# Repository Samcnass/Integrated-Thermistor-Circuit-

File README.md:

# Integrated Thermistor Circuit-
Class/Personal project for an analog integrated thermistor circuit that measures temperature using a simple comparison system with visual feedback using LEDs and console output. 

## Project Overview 

The circuit continuously reads:
- A desired temperature, set using a 10kΩ dial potentiometer
- The room's (or object if attached) temperature with a 10kΩ thermistor (Calibrated using thermometer data)

The system compares the two temperatures and will light up:
- Red LED: if it is too hot
- Blue LED: if it is too cold
- Green LED: if it is just right (within range set in code)

This project is great because it blends analog components, component calibration, and simple boolean logic using an Arduino. It is also easily expandable to other projects. 

A full schematic, PCB design, and Arduino IDE code are available via included folders. 

## Components required for project

| Component                      | Quantity |
|-------------------------------|----------|
| Arduino Uno or Nano           | 1        |
| 10kΩ Analog Thermistor        | 1        |
| 10kΩ Dial Potentiometer       | 1        |
| 10kΩ Resistor                 | 1        |
| 330Ω Resistors                | 3        |
| LEDs (Red, Green, Blue)       | 3        |
| Breadboard + Jumper Wires     | as needed |

## Circuit Description 

- The thermistor forms a voltage divider with a 10kΩ resistor, which is then connected to an analog pin to read temperature
- A dial potentiometer is used to set a desired temperature range from the user 
- The Arduino will compare the thermistor and potentiometer readings and will light up an LED to indicate:
  - **Too cold**: Thermistor reading below lower threshold
  - **Too hot**: Thermistor reading above upper threshold
  - **Just right**: Reading within user-defined range

## Circuit Schematic 

full schematic available in /schematic/ folder. 
This can be opened in KiCAD for viewing.
You can also view the schematic pdf in said folder for easy viewing.
The schematic was done outside of class and was part of a personal project. 

## PCB
Full PCB file is available in /PCB/ folder. 
This can be opened in KiCAD for viewing.
You can also view the PCB png for easy viewing.
The PCB was designed as part of a personal project.

## Arduino IDE Code 

Arduino code to read and compare values is found in the /Code/ folder.
The code includes:
- variable to set desired range (ex: range=3, temperature range is plus or minus 3 away from desired temperature)
- Analog to voltage conversion function for easy reading
- LED boolean logic
- Analog inputs from thermistor and potentiometer
- Calibrated thermistor function to convert voltage to temperature (change depending on thermistor)
- Console output depending on temperature comparison

## Calibration 
The thermistor was calibrated using temperature data from a thermometer.  
There is a Microsoft Excel file located in the /Documents/ folder as well as a png of the calibration plot. 
You may change your thermistor calibration as you see fit

---

## Images
An image of the real-world circuit is in the /Images/ folder. The image is of an Arduino Uno but can be changed with an Arduino Nano if needed. 

## How to use 
1. Wire the circuit according to the schematic
2. Change desired temperature range within code 
3. Upload the code to your board
4. Turn the dial to set your desired temperature 
5. Observe LEDs and Arduino console for live output

## Future Improvements
- Add OLED display for real-time temperature readout instead of using console
- Implement circuit onto a complete PCB board and implement in thermodynamics experiements
  
## License
This project is open-source under the LICENSE

-- 

## Other project uses
I have used this circuit to measure the temperature of a refrigerator to study its heating/cooling processes as well as its coefficient of performance.

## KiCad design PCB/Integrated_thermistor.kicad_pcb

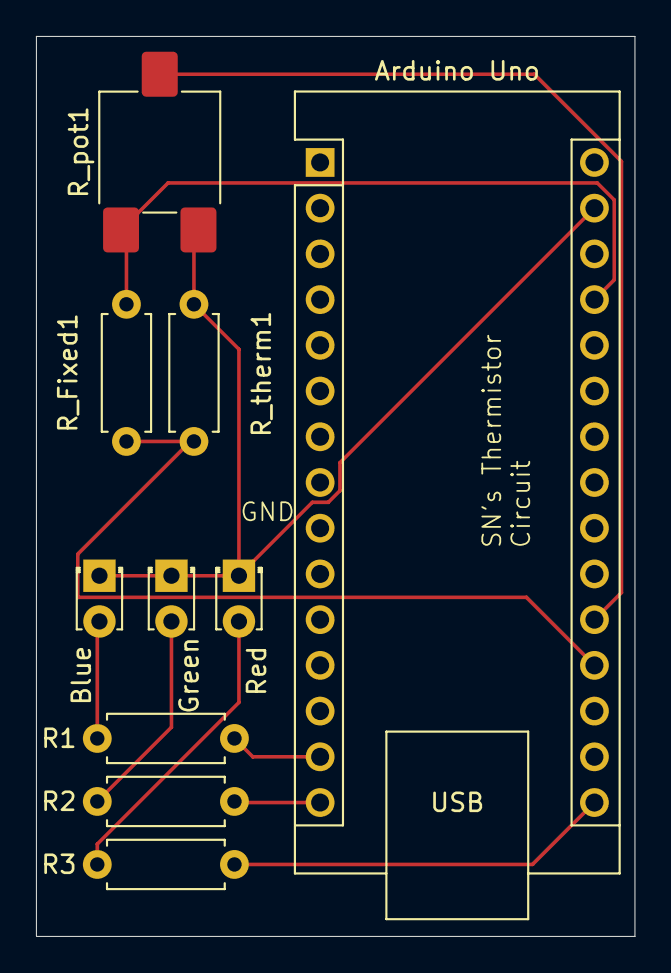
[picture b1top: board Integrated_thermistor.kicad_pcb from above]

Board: 2 copper layers, 33.2 x 50.0 mm, 10 parts (0 on the bottom side), 10 nets.

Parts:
Arduino Uno: Arduino_Nano_v3.x; Arduino_Nano
Blue: 22mA; LED_D1.8mm_W3.3mm_H2.4mm
Green: 22mA; LED_D1.8mm_W3.3mm_H2.4mm
R1, R2, R3: 330Ω; R_Axial_DIN0207_L6.3mm_D2.5mm_P7.62mm_Horizontal
R_Fixed1: 10kΩ; R_Axial_DIN0207_L6.3mm_D2.5mm_P7.62mm_Horizontal
R_pot1: 10kΩ; Potentiometer_ACP_CA6-VSMD_Vertical
R_therm1: 10kΩ; R_Axial_DIN0207_L6.3mm_D2.5mm_P7.62mm_Horizontal
Red: 22mA; LED_D1.8mm_W3.3mm_H2.4mm

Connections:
unnamed: Arduino Uno.27 (+5V), R_Fixed1.1, R_pot1.3
unnamed: Arduino Uno.19 (A0), R_Fixed1.2, R_therm1.1
unnamed: Arduino Uno.20 (A1), R_pot1.2
unnamed: Arduino Uno.14 (D11), R1.2
unnamed: Arduino Uno.15 (D12), R2.2
unnamed: Arduino Uno.16 (D13), R3.2
unnamed: Blue.2 (A), R1.1
unnamed: Arduino Uno.29 (GND), Blue.1 (K), Green.1 (K), R_pot1.1, R_therm1.2, Red.1 (K)
unnamed: Green.2 (A), R2.1
unnamed: R3.1, Red.2 (A)

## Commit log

2025-04-24 Create
2025-04-24 Create schematic_text
2025-04-24 Add schematic KiCAD file and schematic pdf
2025-04-24 Create imgtxt
2025-04-24 image of real-world circuit
2025-04-25 Add integrated thermistor pcb file and png
2025-04-25 Add pcb file and png
2025-04-25 Updated PCB
